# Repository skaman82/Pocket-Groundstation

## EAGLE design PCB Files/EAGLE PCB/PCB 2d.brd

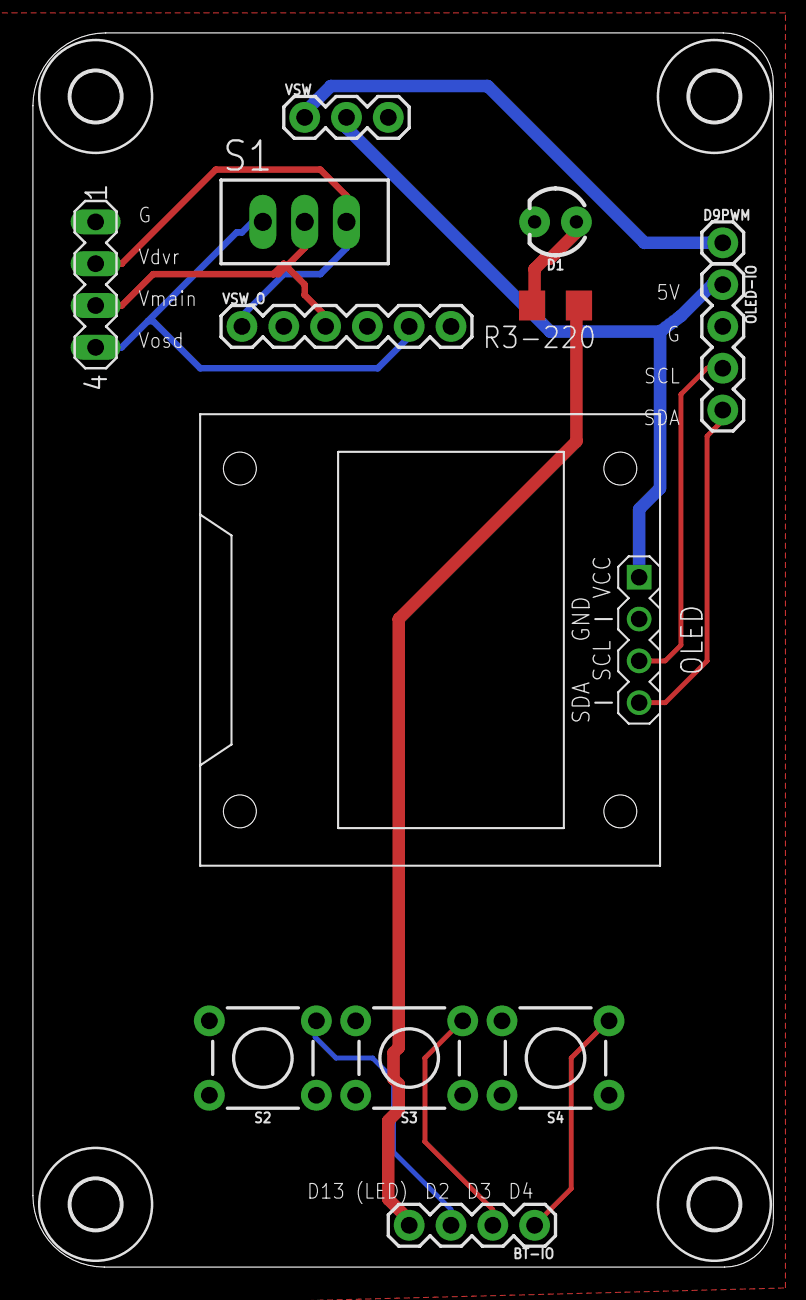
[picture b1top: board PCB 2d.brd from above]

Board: 2 copper layers, 45.0 x 75.0 mm, 17 parts (0 on the bottom side), 13 nets.

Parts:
BT-IO: 1X04
D1: LED_3MM
D9PWM: 1X01
IO3: MA04-1
OLED: DISPLAY-OLED-128X64-I2C
OLED-IO: 1X04
R3-220: 220; R1206
S1: TL32PO; TL3XPO
S2, S3, S4: MOMENTARY-SWITCH-SPST-PTH-6.0MM; TACTILE_SWITCH_PTH_6.0MM
U$2, U$3, U$4, U$5: 3,0
VSW: 1X03
VSW_O: 1X06

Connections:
GND: D1.K, IO3.1, OLED.2, OLED-IO.2, S2.1, S3.1, S4.1, VSW.3, VSW_O.2, VSW_O.4, VSW_O.6
unnamed: D1.A, R3-220.2
unnamed: BT-IO.1, S4.3
unnamed: IO3.3, S1.2, VSW_O.3
unnamed: OLED.1, OLED-IO.1, VSW.2
unnamed: BT-IO.4, R3-220.1
unnamed: OLED.4, OLED-IO.4
unnamed: OLED.3, OLED-IO.3
unnamed: D9PWM.1, VSW.1
unnamed: IO3.2, S1.3, VSW_O.1
unnamed: BT-IO.2, S3.3
unnamed: BT-IO.3, S2.3
VIDOUT: IO3.4, S1.1, VSW_O.5

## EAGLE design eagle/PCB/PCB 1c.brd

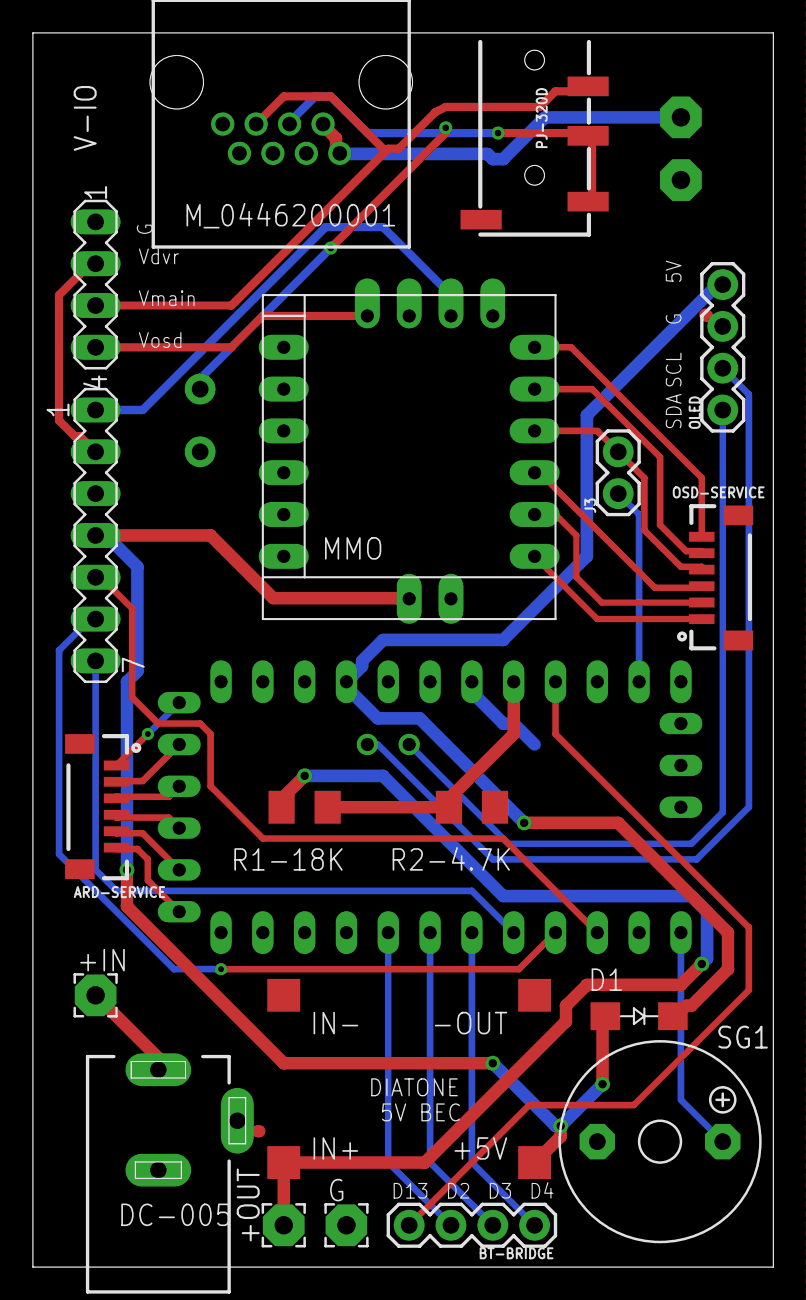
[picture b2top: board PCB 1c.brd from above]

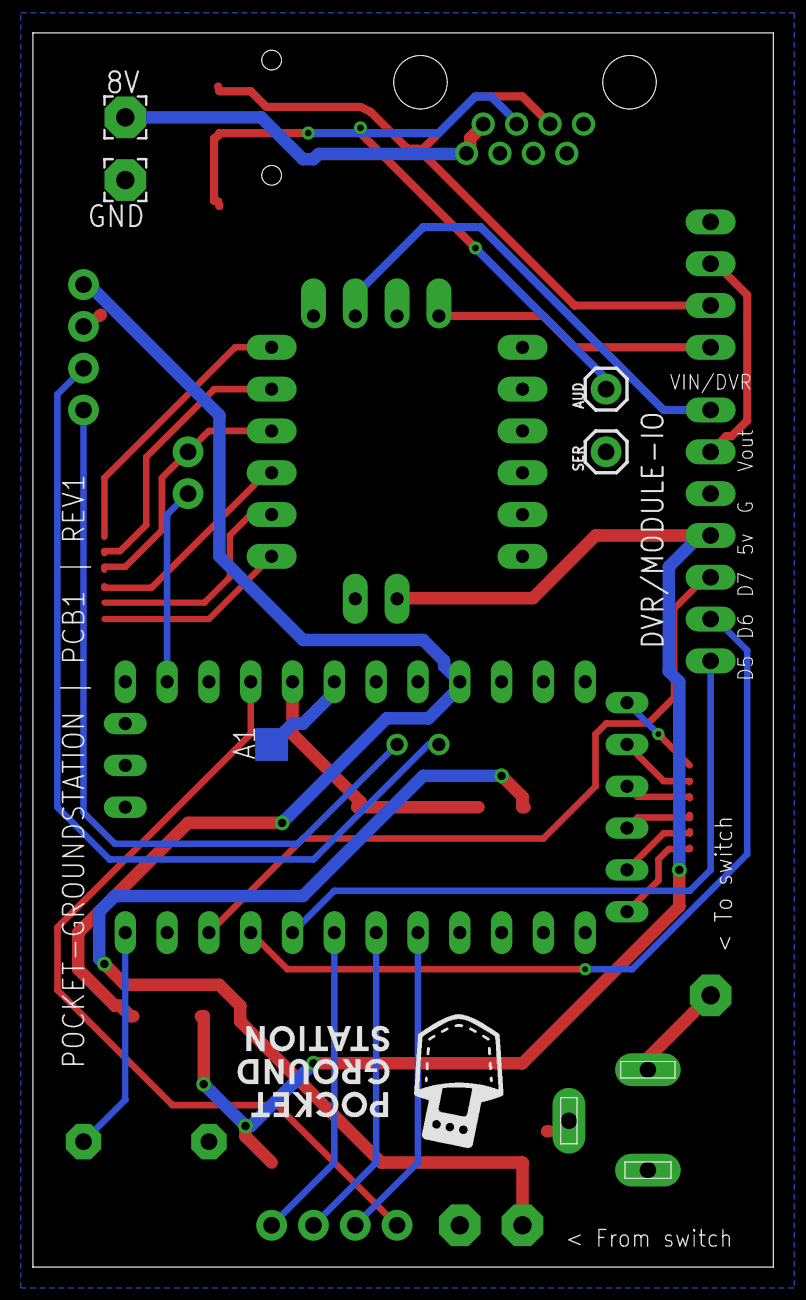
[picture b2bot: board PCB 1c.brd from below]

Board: 2 copper layers, 45.0 x 75.0 mm, 28 parts (5 on the bottom side), 36 nets.

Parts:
8V: 2,54/1,1
+5V: TPTP20SQ; TP20SQ
+IN: 2,54/1,1
+OUT: 2,54/1,1
-OUT: TPTP20SQ; TP20SQ
A1: TPTP20SQ; TP20SQ
ARD-SERVICE: EM406; 1X06-1MM
AUD: 1X01
BT-BRIDGE: 1X04
D1: GF1; SMA-DO214AC
DC-005: DCJ0202
DVR/MODULE-IO: MA07-1
G: 2,54/1,1
GND: 2,54/1,1
IN+: TPTP20SQ; TP20SQ
IN-: TPTP20SQ; TP20SQ
J3: 1X02
MINIMOSD: MICROMINIMOSDPWR; MMOSDNVDVID
M_0446200001: 0446200001
OLED: 1X04
OSD-SERVICE: EM406; 1X06-1MM
PJ-320D: AUDIO_JACK_TRRSSMD_RA; AUDIO_JACK_3.5MM_TRRS_SMD_RA
R1-18K: 18k Ohm; M1206
R2-4.7K: 4.7 kOhm; M1206
SER: 1X01
SG1: F/TMB
U$1: ABK-PRO-MINI
V-IO: MA04-1

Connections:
8V: 8V.1, M_0446200001.7, M_0446200001.8
+: +IN.1, DC-005.1
+5V: +5V.TP, D1.A, DVR/MODULE-IO.4, MINIMOSD.IVCC
+5VFTDI: MINIMOSD.VCC, OSD-SERVICE.3
AUDIO: AUD.1, M_0446200001.5, PJ-320D.RING1, PJ-320D.TIP
BEC-5V: D1.K, OLED.4, U$1.VCC
BUTTON1: BT-BRIDGE.3, U$1.D2
BUTTON2: BT-BRIDGE.2, U$1.D3
BUTTON3: BT-BRIDGE.1, U$1.D4
BUZZER: SG1.+, U$1.D9
D5: DVR/MODULE-IO.7, U$1.D5
D6: DVR/MODULE-IO.6, U$1.D6
D7: DVR/MODULE-IO.5, U$1.D7
D11-RX: J3.1, U$1.D11
DTR: MINIMOSD.DTR, OSD-SERVICE.6
DVRVIDEO-IN: DVR/MODULE-IO.2, V-IO.2
GND: -OUT.TP, DC-005.2, DC-005.3, DVR/MODULE-IO.3, G.1, GND.1, IN-.TP, MINIMOSD.IGND, MINIMOSD.VGND2, M_0446200001.2, M_0446200001.4, OLED.3, PJ-320D.EARTH, R2-4.7K.1, SG1.-, U$1.GND, V-IO.1
GPSTX: MINIMOSD.TX, OSD-SERVICE.5
LED: BT-BRIDGE.4, U$1.D13
unnamed: A1.TP, U$1.A1
unnamed: MINIMOSD.GND1, OSD-SERVICE.2
unnamed: MINIMOSD.GND2, OSD-SERVICE.1
unnamed: ARD-SERVICE.1, U$1.BLK
unnamed: ARD-SERVICE.2, U$1.G
unnamed: ARD-SERVICE.3, U$1.5V
unnamed: ARD-SERVICE.5, U$1.TX01
unnamed: ARD-SERVICE.6, U$1.DTR
OSDSIGNAL: MINIMOSD.VIDOUT, V-IO.4
RAWVIDEO_MODULE: DVR/MODULE-IO.1, MINIMOSD.VIDIN
RX: J3.2, MINIMOSD.RX, OSD-SERVICE.4
SCL: OLED.2, U$1.A5
SDA: OLED.1, U$1.A4
V: ARD-SERVICE.4, U$1.RX01
VCC: +OUT.1, IN+.TP, R1-18K.2
VMAIN: M_0446200001.3, PJ-320D.RING2, V-IO.3
VSENS: R1-18K.1, R2-4.7K.2, U$1.A0

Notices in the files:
parts and their libraries:
diy-modules: Released under the Creative Commons Attribution 4.0 International License: http://creativecommons.org/licenses/by/4.0
SparkFun-Switches: Licensing: Creative Commons ShareAlike 4.0 International - https://creativecommons.org/licenses/by-sa/4.0
